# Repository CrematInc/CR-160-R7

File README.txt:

The CR-160-R7 board is an evaluation board for Cremat Inc's shaping amplifier 
modules (CR-200-X) and baseline restorer module (CR-210).

Included is a bill of materials (BOM) with supplier information.
The CAD files are included and were created by KiCad.
Gerber files and drill file are also included
This is offered as open source hardware under the MIT license.

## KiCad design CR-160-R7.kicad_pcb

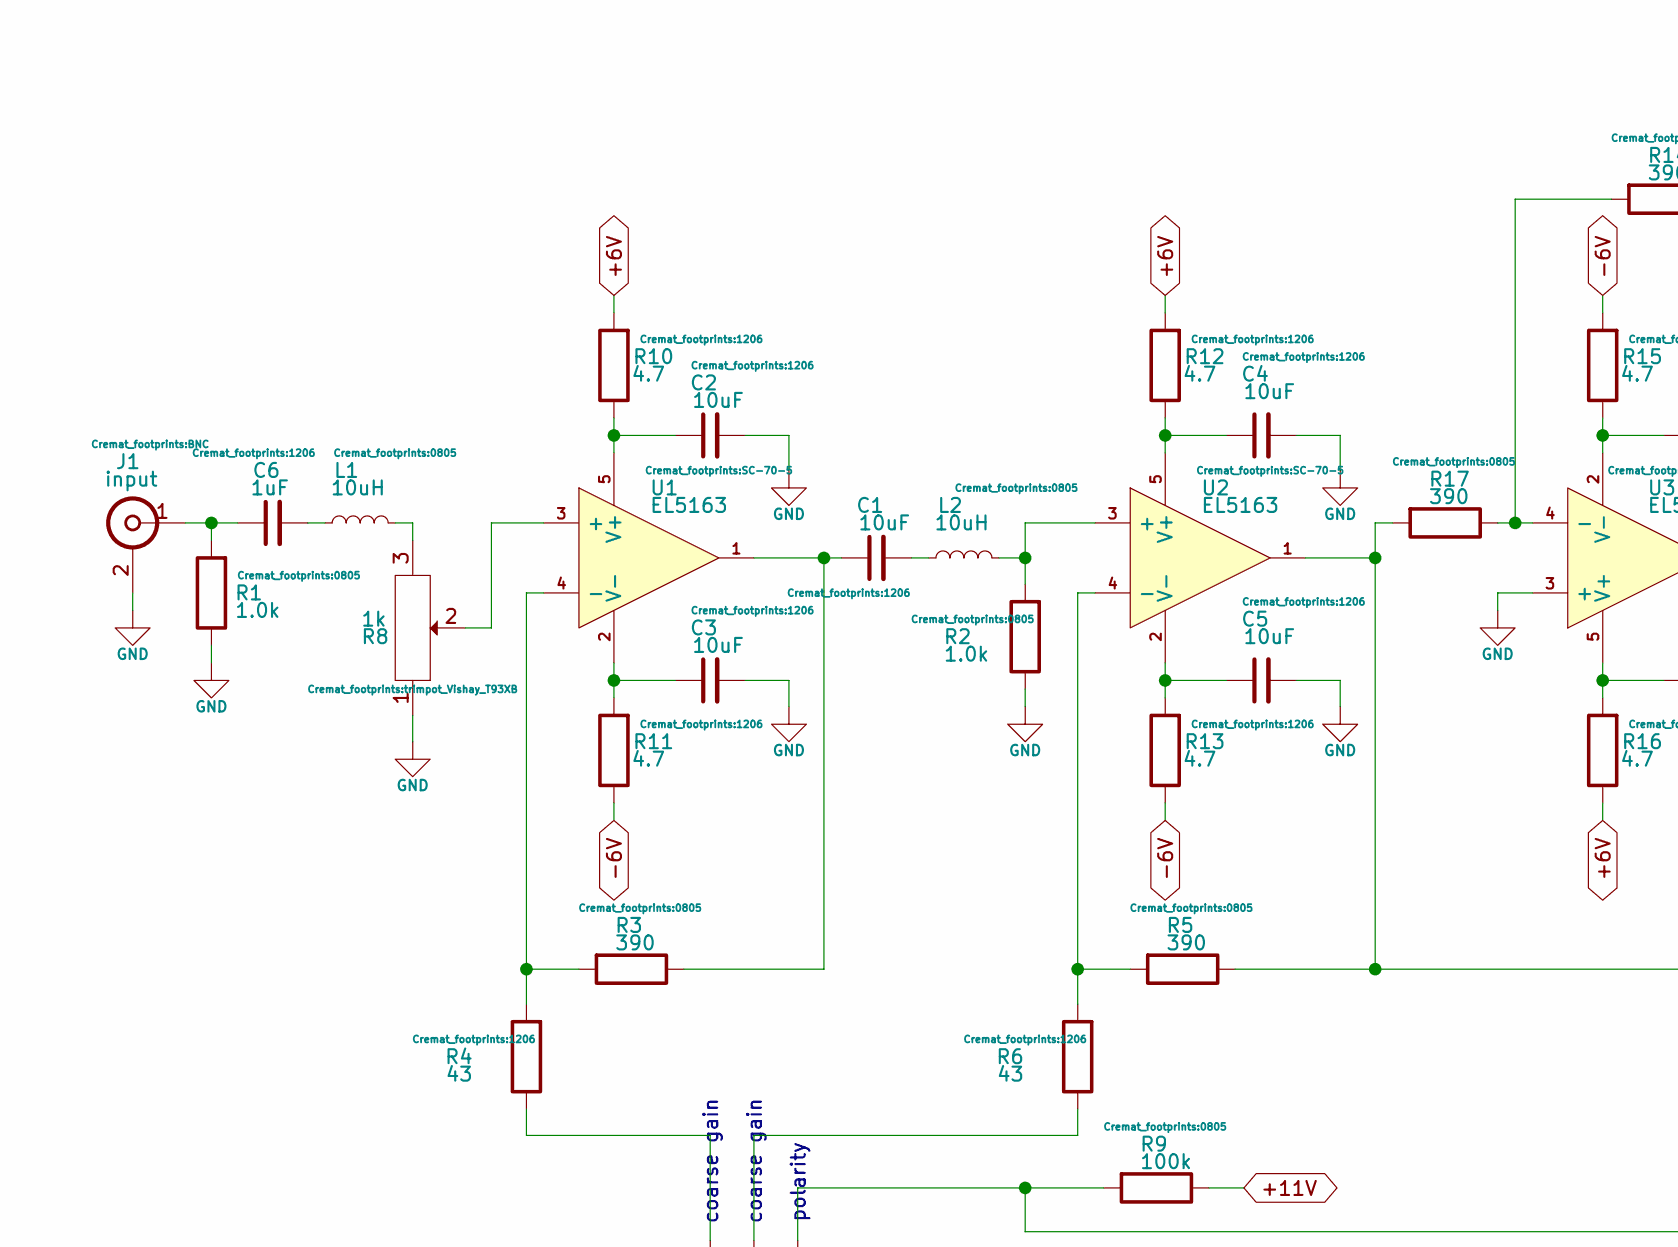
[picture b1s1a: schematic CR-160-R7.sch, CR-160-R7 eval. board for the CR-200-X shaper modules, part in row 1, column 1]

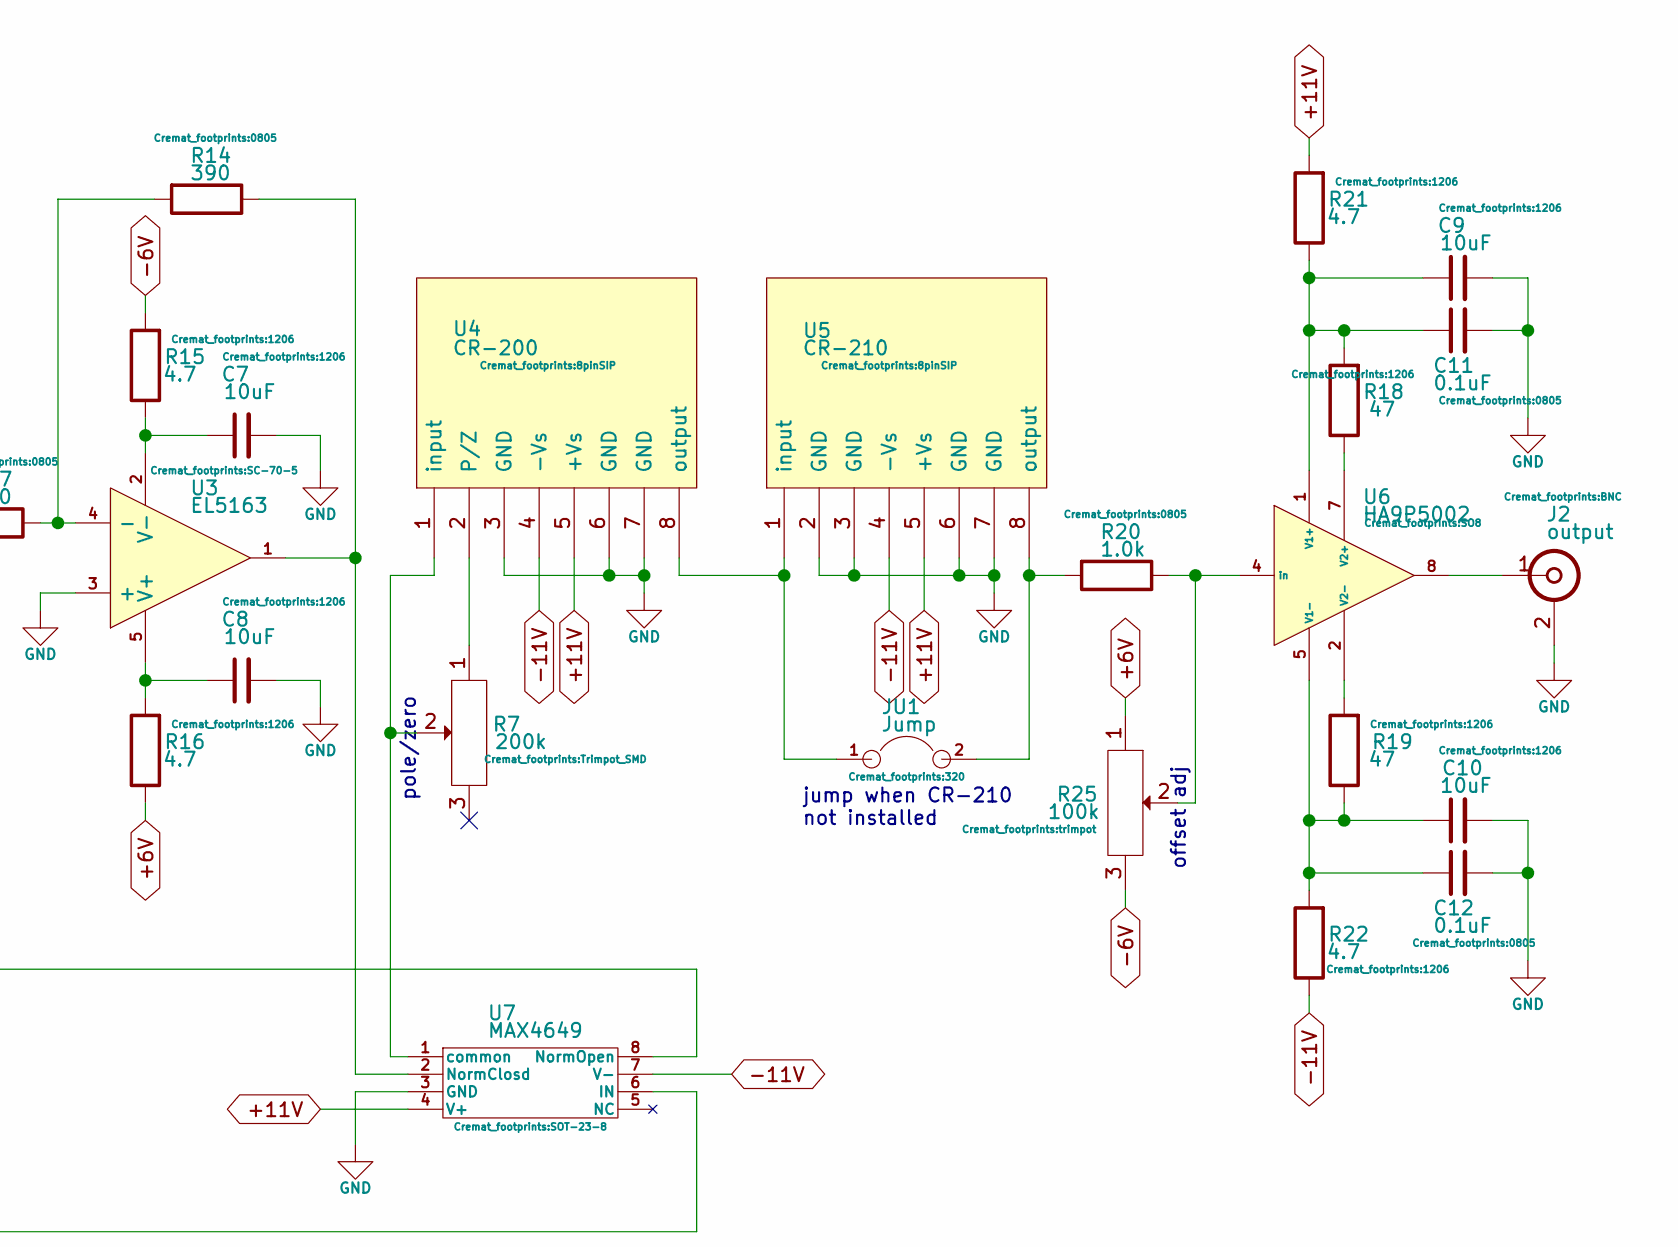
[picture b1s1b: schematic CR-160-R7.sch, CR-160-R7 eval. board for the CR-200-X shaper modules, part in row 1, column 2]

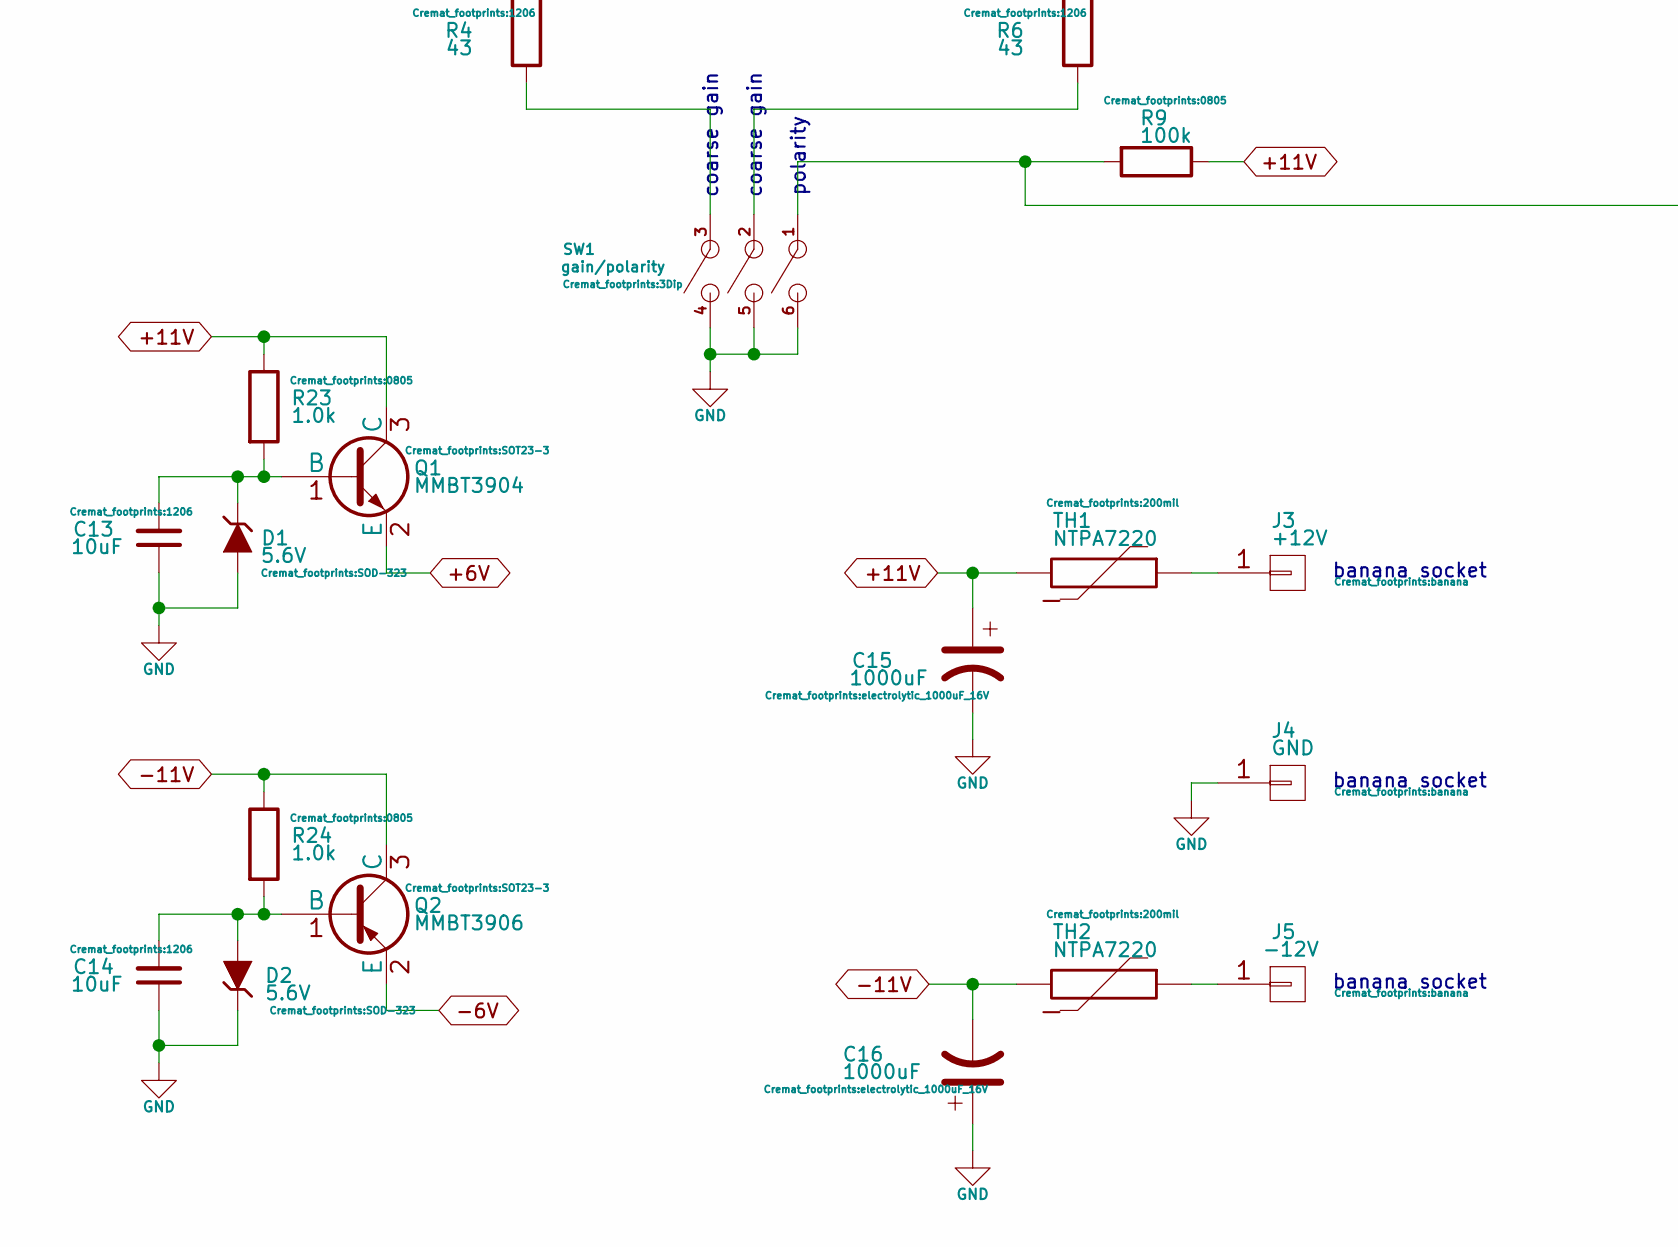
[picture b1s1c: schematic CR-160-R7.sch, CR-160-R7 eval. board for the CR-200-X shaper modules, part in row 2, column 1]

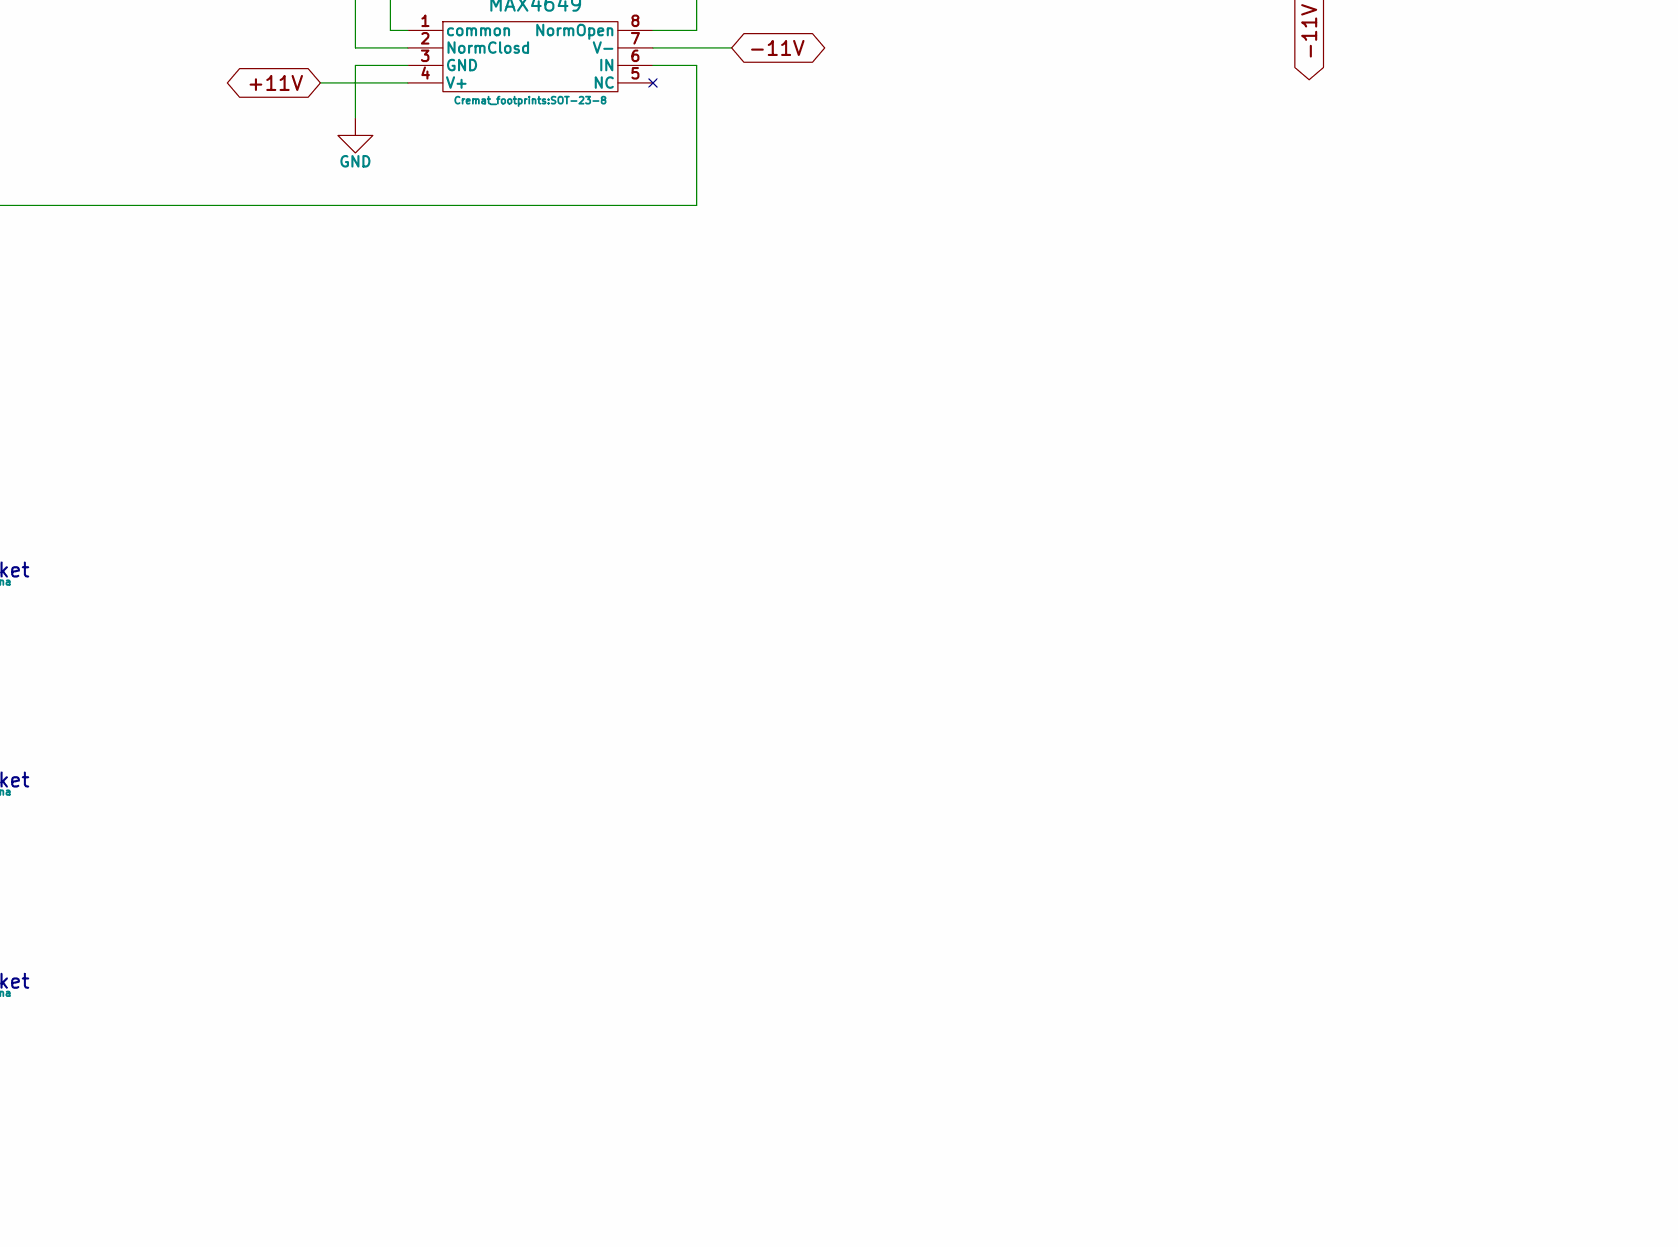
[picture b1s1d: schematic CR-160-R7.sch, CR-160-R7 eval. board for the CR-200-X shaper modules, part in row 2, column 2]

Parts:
C1, C2, C3, C4, C5, C7, C8, C9, C10, C13, C14: 10uF; 1206
C6: 1uF; 1206
C11, C12: 0.1uF; 0805
C15, C16: 1000uF; electrolytic_1000uF_16V
D1, D2: 5.6V; SOD-323
J1: input; BNC
J2: output; BNC
J3: +12V; banana
J4: GND; banana
J5: -12V; banana
JU1: Jump; 320
L1, L2: 10uH; 0805
Q1: MMBT3904; SOT23-3
Q2: MMBT3906; SOT23-3
R1, R2, R20, R23, R24: 1.0k; 0805
R3, R5, R14, R17: 390; 0805
R4, R6: 43; 1206
R7: 200k; Trimpot_SMD
R8: 1k; trimpot_Vishay_T93XB
R9: 100k; 0805
R10, R11, R12, R13, R15, R16, R21, R22: 4.7; 1206
R18, R19: 47; 1206
R25: 100k; trimpot
SW1: gain/polarity; 3Dip
TH1, TH2: NTPA7220; 200mil
U1, U2, U3: EL5163; SC-70-5
U4: CR-200; 8pinSIP
U5: CR-210; 8pinSIP
U6: HA9P5002; SO8
U7: MAX4649; SOT-23-8

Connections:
+6V: Q1.2 (E), R10.2, R12.2, R16.1, R25.1
+11V: C15.1, Q1.3 (C), R9.1, R21.2, R23.1, TH1.2, U4.5 (+Vs), U5.5 (+Vs), U7.4 (V+)
-6V: Q2.2 (E), R11.1, R13.1, R15.2, R25.3
-11V: C16.2, Q2.3 (C), R22.1, R24.1, TH2.2, U4.4 (-Vs), U5.4 (-Vs), U7.7 (V-)
GND: C2.2, C3.2, C4.2, C5.2, C7.2, C8.2, C9.2, C10.2, C11.2, C12.2, C13.1, C14.1, C15.2, C16.1, D1.1 (A), D2.2 (K), J1.2 (Ext), J2.2 (Ext), J4.1, R1.1, R2.1, R8.1, SW1.4, SW1.5, SW1.6, U3.3 (+), U4.3 (GND), U4.6 (GND), U4.7 (GND), U5.2 (GND), U5.3 (GND), U5.6 (GND), U5.7 (GND), U7.3 (GND)
unnamed: C1.1, R3.1, U1.1
unnamed: C1.2, L2.1
unnamed: C2.1, R10.1, U1.5 (V+)
unnamed: C3.1, R11.2, U1.2 (V-)
unnamed: C4.1, R12.1, U2.5 (V+)
unnamed: C5.1, R13.2, U2.2 (V-)
unnamed: C6.1, J1.1 (In), R1.2
unnamed: C6.2, L1.1
unnamed: C7.1, R15.1, U3.2 (V-)
unnamed: C8.1, R16.2, U3.5 (V+)
unnamed: C10.1, C12.1, R19.1, R22.2, U6.5 (V1-)
unnamed: C9.1, C11.1, R18.2, R21.1, U6.1 (V1+)
unnamed: C13.2, D1.2 (K), Q1.1 (B), R23.2
unnamed: C14.2, D2.1 (A), Q2.1 (B), R24.2
unnamed: J2.1 (In), U6.8
unnamed: J3.1, TH1.1
unnamed: J5.1, TH2.1
unnamed: JU1.1, U4.8 (output), U5.1 (input)
unnamed: JU1.2, R20.2, U5.8 (output)
unnamed: L1.2, R8.3
unnamed: L2.2, R2.2, U2.3 (+)
unnamed: R3.2, R4.2, U1.4 (-)
unnamed: R4.1, SW1.3
unnamed: R5.2, R6.2, U2.4 (-)
unnamed: R6.1, SW1.2
unnamed: R7.1, U4.2 (P/Z)
unnamed: R7.2, U4.1 (input), U7.1 (common)
unnamed: R8.2, U1.3 (+)
unnamed: R9.2, SW1.1, U7.6 (IN)
unnamed: R14.1, U3.1, U7.2 (NormClosd)
unnamed: R14.2, R17.1, U3.4 (-)
unnamed: R5.1, R17.2, U2.1, U7.8 (NormOpen)
unnamed: R18.1, U6.7 (V2+)
unnamed: R19.2, U6.2 (V2-)
unnamed: R20.1, R25.2, U6.4 (in)

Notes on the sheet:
pole/zero
offset adj
polarity
coarse gain
banana socket
jump when CR-210 not installed

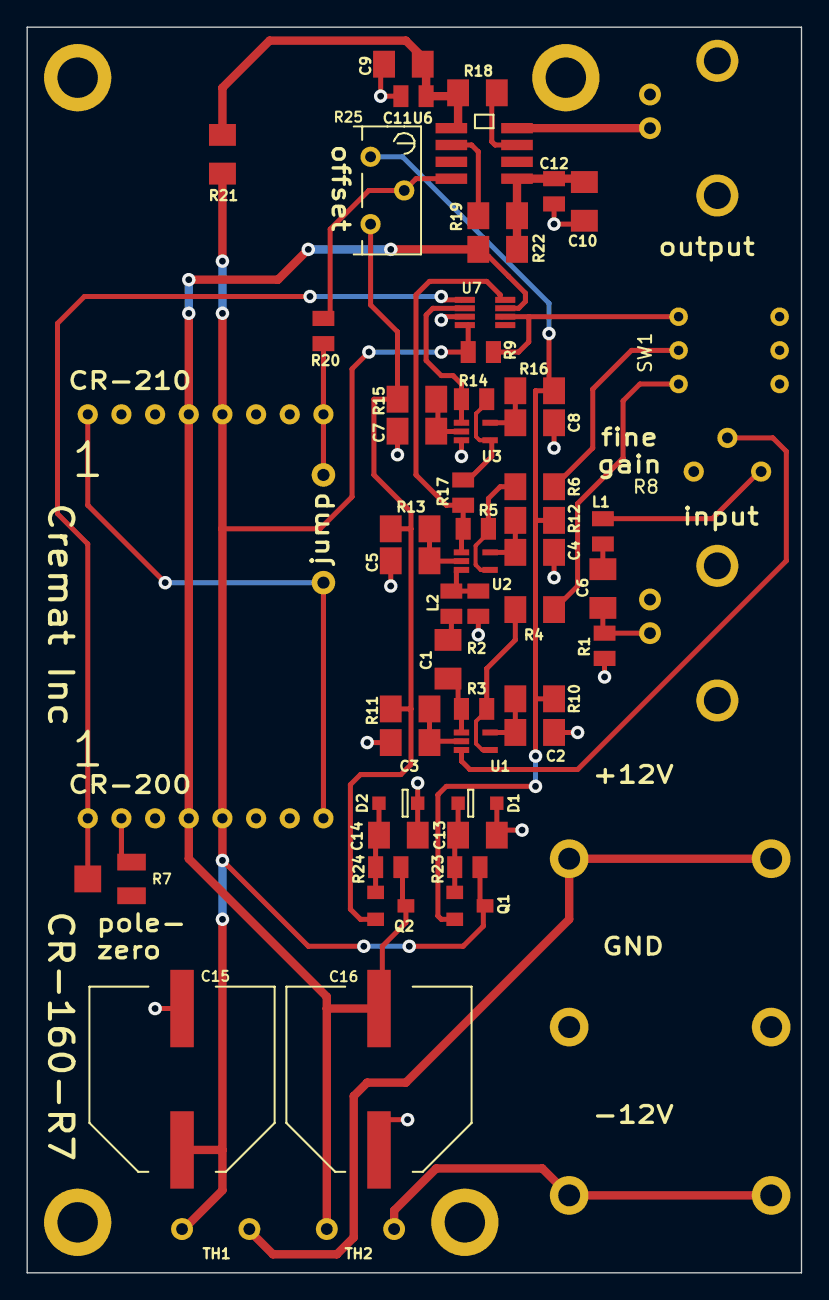
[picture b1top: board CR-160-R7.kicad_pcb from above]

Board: 2 copper layers, 58.4 x 94.0 mm, 63 parts (0 on the bottom side), 40 nets.

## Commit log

2015-11-24 :tada: Added .gitattributes & .gitignore files
2015-11-24 evaluation board for Cremat's shaping amplifier modules CR-200-X and CR-210
    KiCad files, Gerber files, schematic, layout image, bill of materials
    (BOM)

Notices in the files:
CR-160-R7.sch:
This is Open Source Hardware under the MIT license. http://opensource.org/licenses/MIT
